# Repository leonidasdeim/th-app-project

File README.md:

# Home app project
Full solution for temperature &amp; humidity indoor monitoring. 
But main goal of the project is to add more and more home monitoring and automation functionality.

## Project structure and stack
- `th-api` - server written in *Java/SpringBoot* and *PostreSQL, Docker*.
- `th-web` - client written in *JavaScript* with *React*.
- `th-board` - PCB schematics and board, *KiCad* project.
- `th-esp` - sensor sources written with *Arduino* libraries.
- `docs` - other files

## Client preview

~~Project is published, you can check it here:
https://deimantas.tech/th/~~

Screenshot/preview of one sensor measurements:

## Sensor

Temperature and humidity sensor board is based on `ESP8266` microcontroller in the `ESP-12F` (or `ESP-12E`) module.
For measurements `DHT11` sensor is used

PCB Render and assembled vew:

## Workflow

After sensor has been turned on for the first time, it will create WiFi AP. Connect to it using your phone to configure it. You will need to enter your home WiFi info and an email of your `deimantas.tech/th` account, so sensor will register itself to your account. If something goes wrong you can always reset your sensor by pressing `reset button` while holding `user button`. After successfull configuration sensor should appear in Settings tab of the client app.

## Running locally

### Server side

To start API and database the simplest way would be to run it in docker container. Run this command in *th-app-project/th-api* folder:

`docker-compose up`

### Client

To start client application run these regular React commands in *th-app-project/th-web* folder:

`npm install`

`npm start`

> Don't forget to change API url to your own server address :)

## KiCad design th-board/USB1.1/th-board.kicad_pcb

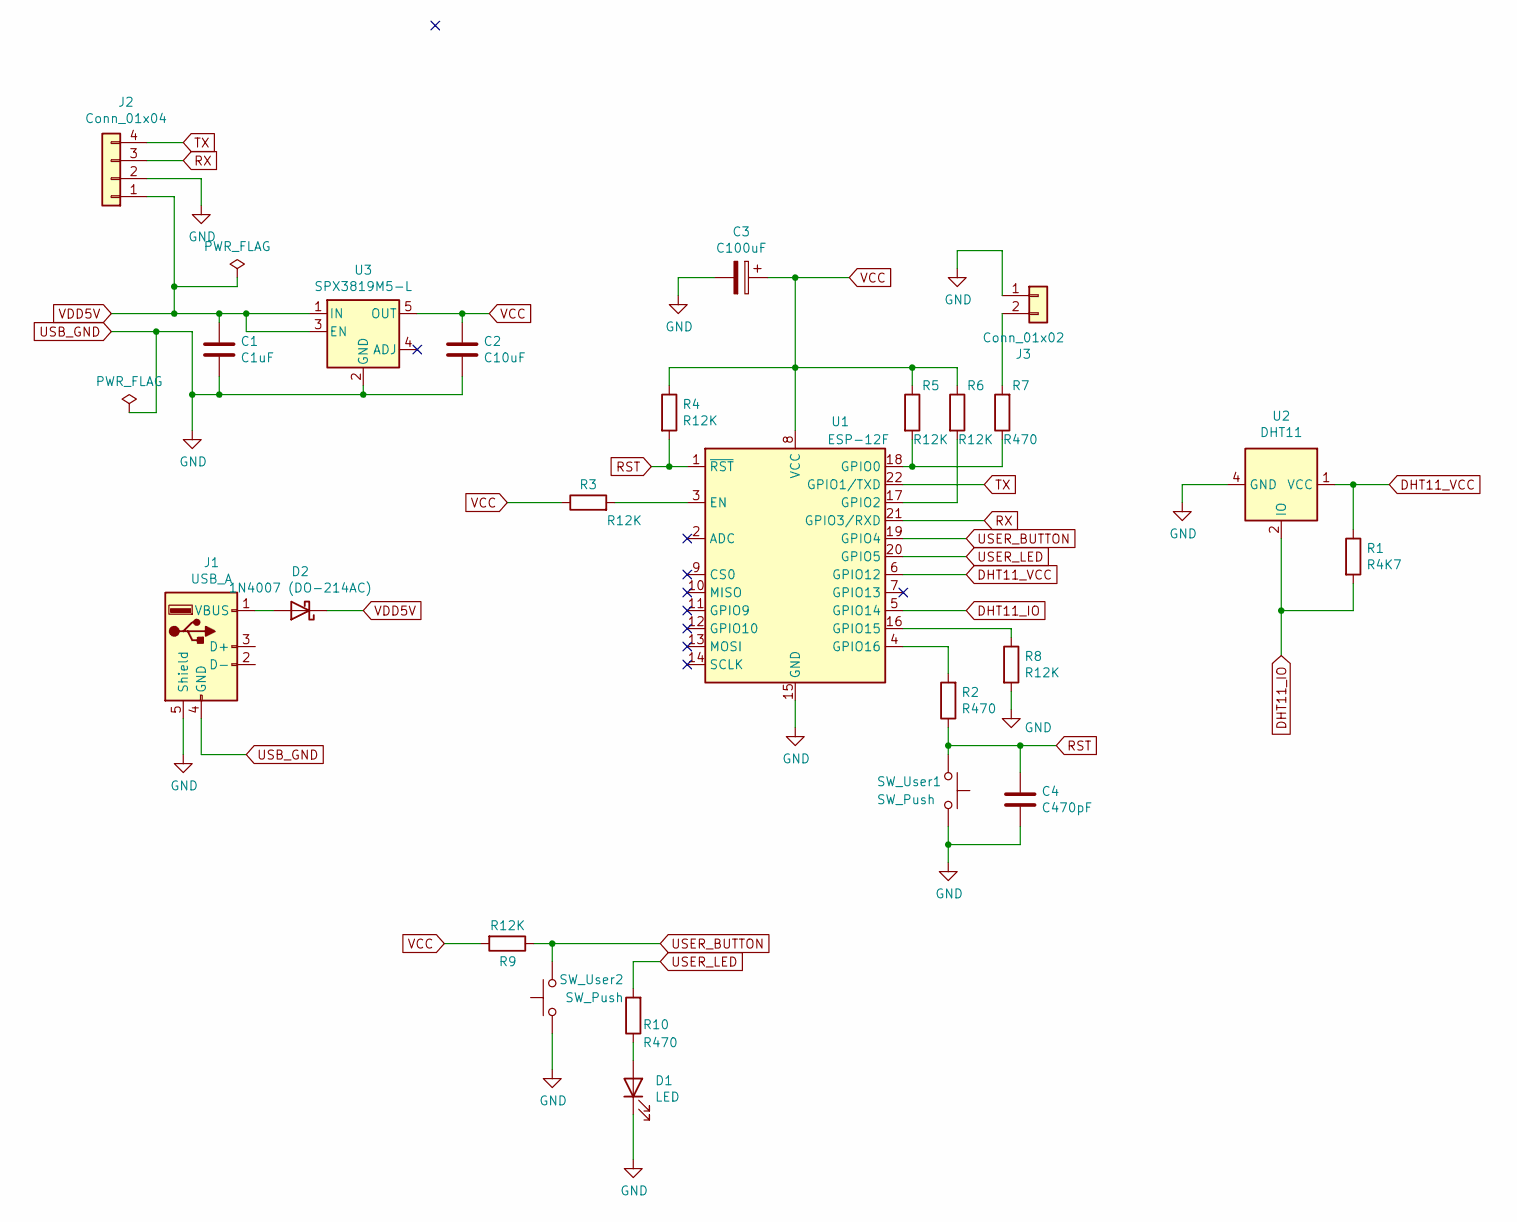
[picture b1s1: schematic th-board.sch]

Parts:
C1: C1uF; C_0805_2012Metric
C2: C10uF; C_0805_2012Metric
C3: C100uF; CP_EIA-6032-28_Kemet-C
C4: C470pF; C_0805_2012Metric
D1: LED; LED_0805_2012Metric
D2: 1N4007 (DO-214AC); D_SMA
J1: USB_A; USB_A_Molex_67643_Horizontal
J2: Conn_01x04; PinHeader_1x04_P2.54mm_Vertical
J3: Conn_01x02; PinHeader_1x02_P2.54mm_Vertical
R1: R4K7; R_0805_2012Metric
R2, R7, R10: R470; R_0805_2012Metric
R3, R4, R5, R6, R8, R9: R12K; R_0805_2012Metric
SW_User1, SW_User2: SW_Push; SW_SPST_FSMSM
U1: ESP-12F; ESP-12E
U2: DHT11; Aosong_DHT11_5.5x12.0_P2.54mm
U3: SPX3819M5-L; SOT-23-5

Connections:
DHT11_IO: R1.2, U1.5 (GPIO14), U2.2 (IO)
DHT11_VCC: R1.1, U1.6 (GPIO12), U2.1 (VCC)
unnamed: D1.2 (A), R10.1
unnamed: D2.2 (A), J1.1 (VBUS)
unnamed: J3.2, R7.2
unnamed: R2.2, U1.4 (GPIO16)
unnamed: R3.2, U1.3 (EN)
unnamed: R5.2, R7.1, U1.18 (GPIO0)
unnamed: R6.2, U1.17 (GPIO2)
unnamed: R8.1, U1.16 (GPIO15)
RST: C4.1, R2.1, R4.2, SW_User1.1, U1.1 (~RST); also elsewhere on the board
RX: J2.3, U1.21 (GPIO3/RXD)
TX: J2.4, U1.22 (GPIO1/TXD)
USB_GND: C1.2, C2.2, C3.2, C4.2, D1.1 (K), J1.4 (GND), J1.5 (Shield), J2.2, J3.1, R8.2, SW_User1.2, SW_User2.1, U1.15 (GND), U2.4 (GND), U3.2 (GND); also elsewhere on the board
USER_BUTTON: R9.1, SW_User2.2, U1.19 (GPIO4); also elsewhere on the board
USER_LED: R10.2, U1.20 (GPIO5)
VCC: C2.1, C3.1, R3.1, R4.1, R5.1, R6.1, R9.2, U1.8 (VCC), U3.5 (OUT)
VDD5V: C1.1, D2.1 (K), J2.1, U3.1 (IN), U3.3 (EN)

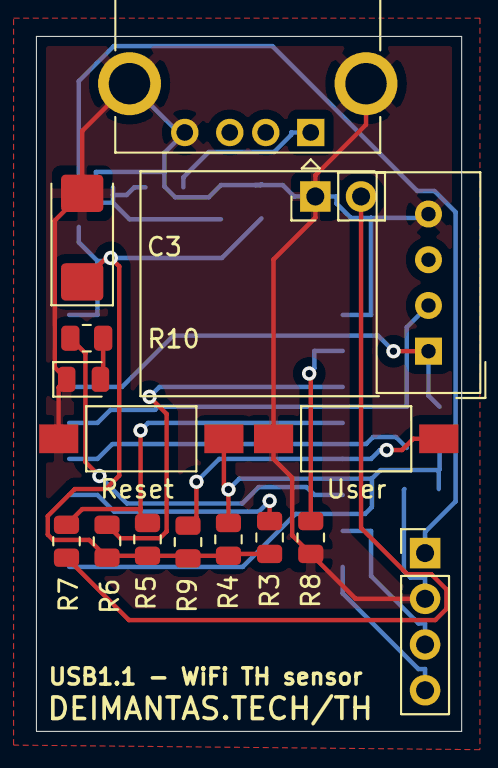
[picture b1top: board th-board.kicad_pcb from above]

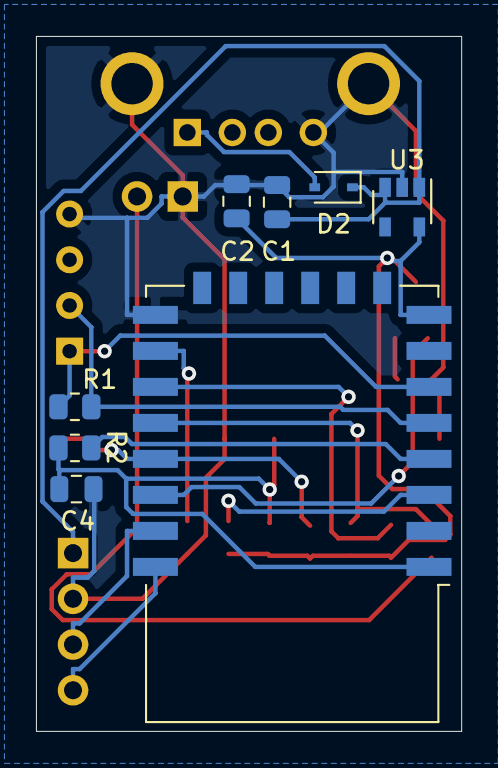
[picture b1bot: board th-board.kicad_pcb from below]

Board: 2 copper layers, 23.6 x 38.6 mm, 24 parts (8 on the bottom side), 18 nets.

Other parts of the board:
Reset: SW_Push; SW_SPST_FSMSM
User: SW_Push; SW_SPST_FSMSM

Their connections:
RST: Reset.1; also elsewhere on the board
USB_GND: Reset.2, User.1; also elsewhere on the board
USER_BUTTON: User.2; also elsewhere on the board

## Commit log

2021-11-19 Initial
2021-11-19 Docker added
2021-11-22 Sensor registration API side
2021-11-22 Fixes for registration
2021-11-22 Naming changes
2021-11-22 Swagger ui added
2021-11-22 Get all sensors endpoint added
2021-11-22 Dummy temp and humidity
2021-11-24 postgresql added, swagger removed
2021-11-24 Get measurements only for a day
2021-11-24 Initial web app (recharts based)
2021-11-26 Measurement reading and simple state machine added
2021-11-26 Kicad project initial
2021-12-01 First version of pcb
2021-12-01 Led added to pcb, v1.1
2021-12-03 Wifi configuration handling added, some rework regarding sensor verification
2021-12-08 WEB: dashboards initial
2021-12-08 Cleanup/Fixes
2021-12-08 Double chart added
2021-12-08 WEB: More cleanup
2021-12-09 WEB: new icons
2021-12-09 PCB: new board
2021-12-20 PCB: smaller board
2021-12-20 WEB: fetch different sensors
2021-12-21 API: authentication
2021-12-21 PCB: very small pcb :)
2021-12-21 API: areas added
2021-12-22 WEB: new template
2021-12-22 WEB: redux for meas. data added
2021-12-23 WEB: login initial
2021-12-23 WEB: reformat all files
2021-12-23 WEB: logout implemented
2021-12-23 WEB: fetch sensors and handle api error
2021-12-23 API: config
2021-12-23 WEB: measurement data fetching initial
2021-12-25 WEB: area API and sidebar areas section
2021-12-25 WEB: door icons for areas
2021-12-25 WEB: adding graphs initial
2021-12-26 WEB: main dashboard
2021-12-26 WEB: area dashboard
2021-12-30 API: register manufactured devices feature
2021-12-30 WEB: current stats for areas
2021-12-31 WEB: settings page initial
2022-01-07 API: new sensor registration
2022-01-07 PCB: some rearranges
2022-01-07 API: java 17
2022-01-10 ESP: register sensor automatically on setup
2022-01-10 API: automatic sensor registration
2022-01-18 API: disable cors
2022-01-18 WEB: settings area manager initial
2022-01-24 API: fix bug for updating area of sensor
2022-01-24 WEB: device settings added
2022-01-24 API: some fixes
2022-01-24 WEB: preparing to publish
2022-01-24 WEB: warning fixes
2022-01-24 WEB: remove whitespaces
2022-01-26 WEB: more fixes after publishing
2022-02-19 WEB: registration
2022-02-19 API: sonar fixes
2022-02-19 WEB: homepage fix
2022-02-19 WEB: Update package.json
2022-02-19 WEB: table fixes for small screens
2022-02-19 WEB: no devices alert and device status indicator
2022-02-19 WEB: small ui improvements
2022-02-19 API: dockerfile update
2022-02-19 PCB: update for V1.1 support
2022-02-19 Bump follow-redirects from 1.14.7 to 1.14.9 in /th-web
    Bumps [follow-redirects](https://github.com/follow-redirects/follow-redirects) from 1.14.7 to 1.14.9.
    - [Release notes](https://github.com/follow-redirects/follow-redirects/releases)
    - [Commits](https://github.com/follow-redirects/follow-redirects/compare/v1.14.7...v1.14.9)
    ---
    updated-dependencies:
    - dependency-name: follow-redirects
2022-02-21 PCB: new board 'usb dongle'
2022-02-23 PCB: add ground fill
